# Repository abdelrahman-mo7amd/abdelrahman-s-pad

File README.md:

# Abdelrahman's Macropad ✨

A small, one-handed macro controller built to be portable, practical, and customizable. Perfect for travelers, streamers, hybrid workers, or anyone who wants to speed up their workflow.

---

## Overview

This macropad is designed for **speed and portability**. The macropad provides quick access to your key shortcuts, regardless of whether you're working with video, streaming, or controlling your computer's controls. Macropads allow you fast deployment; simple usage; easily stored.
---

## Features

* **Single-row design**: Simple design with a low profile
* **One-handed**: One-handed access to your frequently used macros
* **Small size**: Easily fits into a bag or sleeve
* **Fully customizable**: Every key can be programmed to a shortcut, media, or macro

---

## Why This Macropad?

This macropad is all about **speed and portability**. Whether you’re editing, streaming, or controlling your system, it gives you instant access to your most important shortcuts. It’s quick to deploy, easy to use, and just as easy to store.

---

## Schematic & PCB:

| Schematic                 | PCB Layout        | Case Fitment         |
| ------------------------- | ----------------- | -------------------- |
|  |  |  |

---

## How to Use It:

1. Connect the macropad via USB (or your preferred connection).
2. Flash your chosen keymap, either the default one or your own.
3. Assign each key to a shortcut, media control, or macro.
4. When you’re done, lay it flat and store, no cables or keys will get in the way.

---

## 📦 What You’ll Need (BOM)

| Quantity | Component          | Description          |
| -------- | ------------------ | -------------------- |
| 4        | Cherry MX Switches | Mechanical switches  |
| 1        | Seeed XIAO RP2040  | Microcontroller      |
| 4        | Blank DSA Keycaps  | Keycaps for switches |
| 4        | M3 × 16 Bolts      | Mounting hardware    |
| 4        | M3 Heatset Inserts | For secure assembly  |
| –        | 3D printed parts   | Custom case          |

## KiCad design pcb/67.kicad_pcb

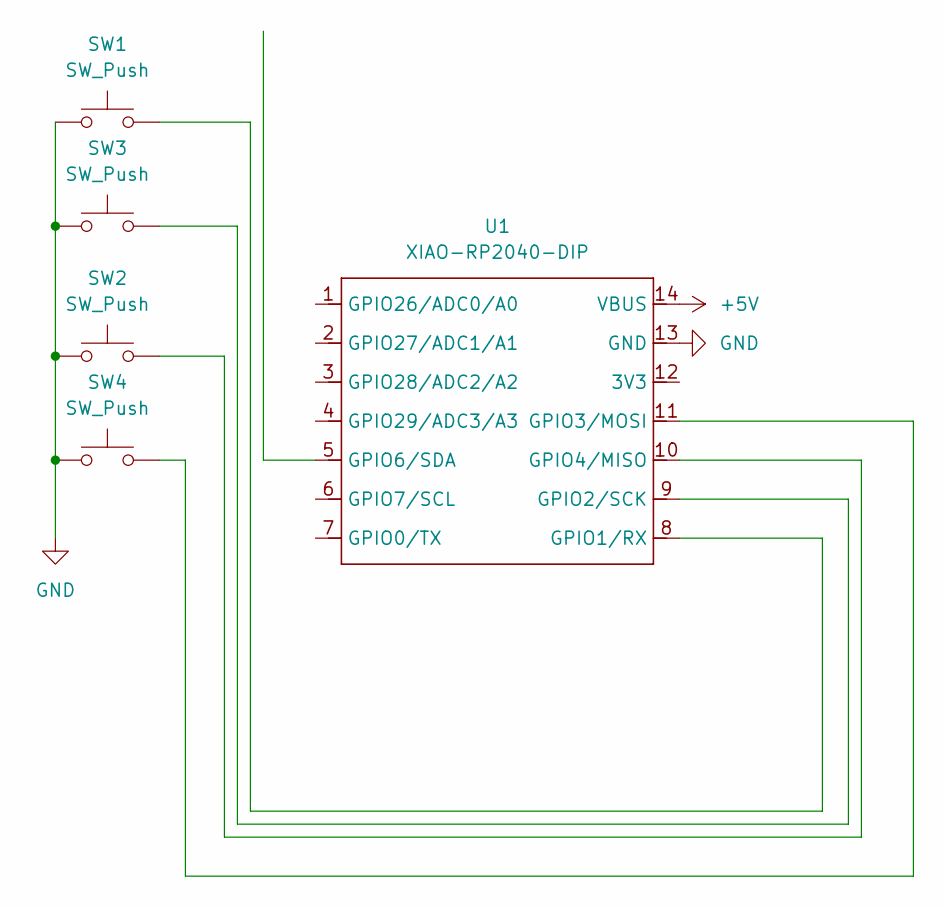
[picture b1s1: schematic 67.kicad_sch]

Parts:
SW1, SW2, SW3, SW4: SW_Push; SW_Cherry_MX_1.00u_PCB
U1: XIAO-RP2040-DIP

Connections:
+5V: U1.14 (VBUS)
GND: SW1.1, SW2.1, SW3.1, SW4.1, U1.13 (GND)
unnamed: SW1.2, U1.8 (GPIO1/RX)
unnamed: SW3.2, U1.9 (GPIO2/SCK)
unnamed: SW4.2, U1.11 (GPIO3/MOSI)
unnamed: SW2.2, U1.10 (GPIO4/MISO)

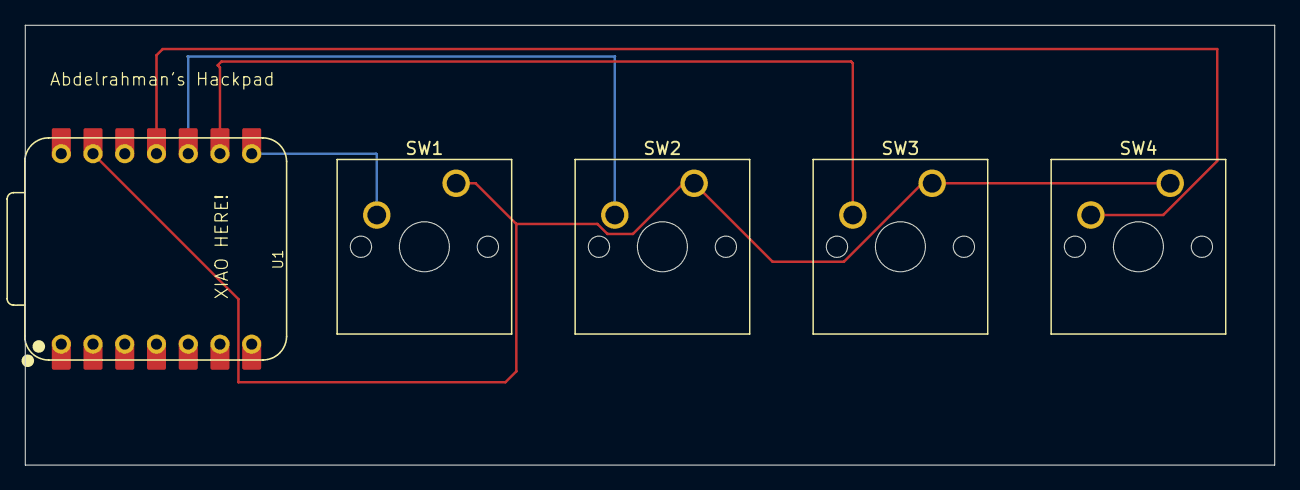
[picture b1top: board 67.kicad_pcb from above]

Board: 2 copper layers, 100.0 x 35.2 mm, 5 parts (0 on the bottom side), 5 nets.

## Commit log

2026-02-14 Revise README for Abdelrahman's Macropad
    Updated the README to reflect new branding and features.
2026-02-14 Fix formatting in usage instructions
